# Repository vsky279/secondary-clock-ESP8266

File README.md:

# Driving secondary clock by ESP8266

Check out this Youtube [video](http://www.youtube.com/watch?v=zKabXwngn9Y) to see the clock in work.

## Intro

I have received this beautiful secondary clock [IPJ0612](https://www.pragotron.sk/?ukaz=content/ipj0612) produced by Czech company Pragotron in 80's. Secondary here means that the clock is only a "display" and has to receive signals from a central clock to move by one minute.

The clock is driven by kind of a stepper motor, powered by 24V. It has two wires as input directly connected to the coil. For one half turn an impulse of 24V is required for the remaining half turn -24V are applied.

## Electronics

We needed to use a circuit that can revert the voltage on its output. Two inputs are connected to ESP8266 GPIOs (GPIO0 and GPIO2). GPIO0 set to high makes 24V on output. Setting GPIO2 high causes -24V on output. A pull-up resistors are connected to GPIOs so that ESP8266 boots in desired 'normal operation' mode. A protection transistor (QX on the scheme) for accidental highs on both inputs has been added. The ESP8266 ESP-01 version is used.

We have used Eagle to draw the [scheme](./hw/driver.sch) and design the [board](./hw/board.sch).

To get the 3.3 voltage to power the ESP8266 a LM1085IT-3.3 TO220 regulator is used.
In my implementation, I'm using step-down module as I had one spare at home (the component with annoying blue LED on the pictures below). It's sold on eBay and can be found as [3A 9V/12V/19V To 3.3V DC-DC USB Step Down Buck Power Supply Module For Car](https://www.ebay.com/sch/i.html?_odkw=2pcs+3A+9V%2F12V%2F19V+To+3.3V+DC-DC+USB+Step+Down+Buck+Power+Supply+Module+For+Car&_osacat=0&_from=R40&_trksid=p2045573.m570.l1313.TR0.TRC0.H0.X3A+9V%2F12V%2F19V+To+3.3V+DC-DC+USB+Step+Down+Buck+Power+Supply+Module+For+Car.TRS0&_nkw=3A+9V%2F12V%2F19V+To+3.3V+DC-DC+USB+Step+Down+Buck+Power+Supply+Module+For+Car&_sacat=0). 

## Programming

I am using NodeMCU Lua ([https://github.com/nodemcu/nodemcu-firmware](https://github.com/nodemcu/nodemcu-firmware)) to program the ESP8266. The programming in Lua is very easy so the core program can have less than 140 lines including the web server used to adjust the clock.

A [NodeMCU custom builds](https://nodemcu-build.com/) tool can be used to compile the binary for ESP8266. Beside standard modules the following modules are used: `cron, enduser_setup, rtctime, sntp`. I have used the integer version of the firmware is used. Though float version should be fine too.

I am using [ESP8266 Flasher](https://github.com/nodemcu/nodemcu-flasher) to flash the binary.

To upload Lua files and files used by the web server the [ESPlorer](https://esp8266.ru/esplorer/) GUI can be used.

The program connects to the WIFI, regularly synchronizes time via NTP and sends 300ms to GPIO0 and GPIO1 alternately. To show correct time ESP needs to know what time the clock is showing at startup so it can set it to actual time. This can be adjusted in web browser as the ESP8266 is running a web server. Otherwise the clock assumes correct time is displayed and sends signals as time goes on.

It exposes also a telnet server so an OTA-like update of Lua codes can be performed.

In my implementation am using only 18V to run the clock (a power adapter from an old printer). With 24V the signal could probably be shorter than 300ms so clock adjustment would be faster.

The source code is in the folder [lua_code](https://github.com/vsky279/secondary-clock-ESP8266/tree/master/lua_code).

## Assembly

A 3d printed [holder](./holder/holder.skp) (designed in SketchUp) and double face duck tape has been used to mount the board inside the clock. An [STL file](./holder/holder.stl) is usually used in the slicer software.

I have also designed a cap to cover the hole of the original connector ([SketchUp file](./hw/holder/cap.skp) and [STL file](./holder/cap.stl)) - not shown on any of photos.

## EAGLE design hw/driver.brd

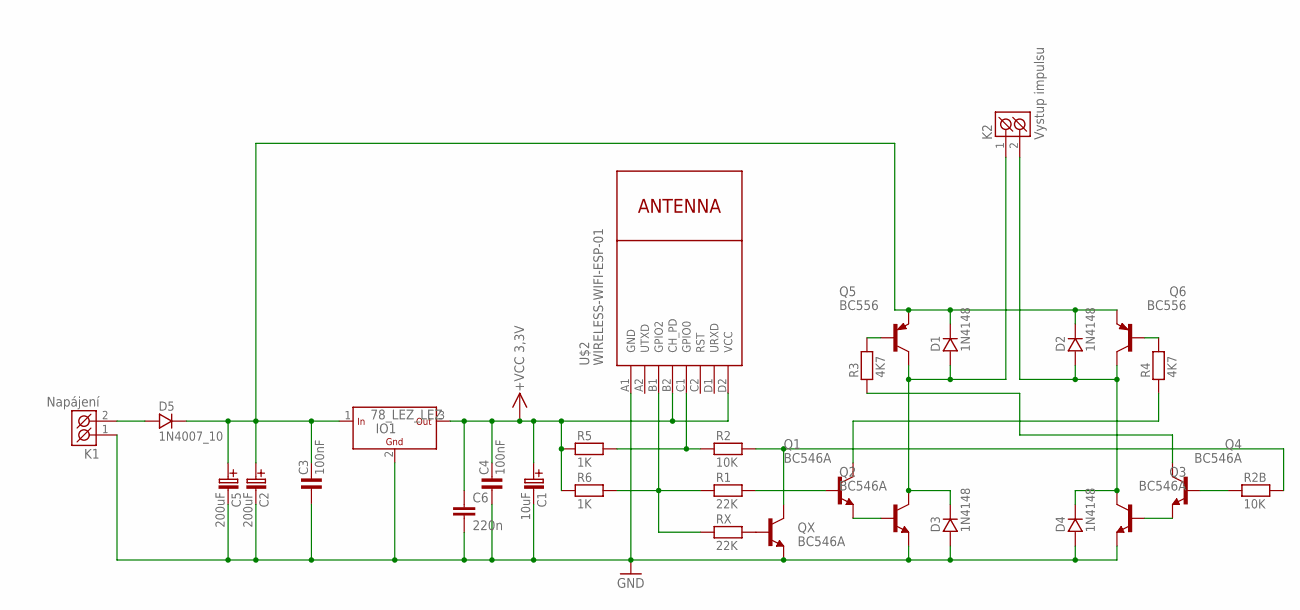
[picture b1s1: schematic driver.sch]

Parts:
C1: 10uF; C-EL_2,5
C2, C5: 200uF; C-EL_5
C3, C4: 100nF; C-5
C6: 220n; C1206
D1, D2, D3, D4: 1N4148; DO35
D5: 1N4007_10; DO41
IO1: 78_LEZ_LEZ; TO-220
K1: Napájení; CZM_5/2
K2: Vystup impulsu; CZM_5/2
Q1, Q2, Q3, Q4: BC546A; TO92-EBC
Q5, Q6: BC556; TO92-EBC
QX: BC546A; TO92-EBC
R1: 22K; R-10
R2, R2B: 10K; R-10
R3, R4: 4K7; R-10
R5, R6: 1K; R-10
RX: 22K; R-10
U$2: WIRELESS-WIFI-ESP-01

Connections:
GND: C1.C- (C_EL-), C2.C- (C_EL-), C3.1, C4.1, C5.C- (C_EL-), C6.2, D3.A, D4.A, IO1.2 (GND), K1.1 (K1), Q2.E, Q3.E, QX.E, U$2.A1 (GND)
unnamed: D2.A, D4.K, K2.2 (K2), Q3.C, Q6.C
unnamed: D1.A, D3.K, K2.1 (K1), Q2.C, Q5.C
unnamed: C2.C+ (C_EL+), C3.2, C5.C+ (C_EL+), D1.K, D2.K, D5.K, IO1.1 (IN), Q5.E, Q6.E
unnamed: Q5.B, R3.2
unnamed: Q6.B, R4.2
unnamed: Q4.C, R3.1
unnamed: Q1.C, R4.1
unnamed: Q4.B, R2B.1
unnamed: Q3.B, Q4.E
unnamed: Q1.E, Q2.B
unnamed: D5.A, K1.2 (K2)
unnamed: Q1.B, R1.2
unnamed: R1.1, R6.2, RX.1, U$2.B1 (GPIO2)
unnamed: QX.C, R2.2, R2B.2
unnamed: R2.1, R5.2, U$2.C1 (GPIO0)
unnamed: QX.B, RX.2
VCC: C1.C+ (C_EL+), C4.2, C6.1, IO1.3 (OUT), R5.1, R6.1, U$2.B2 (CH_PD), U$2.D2 (VCC)

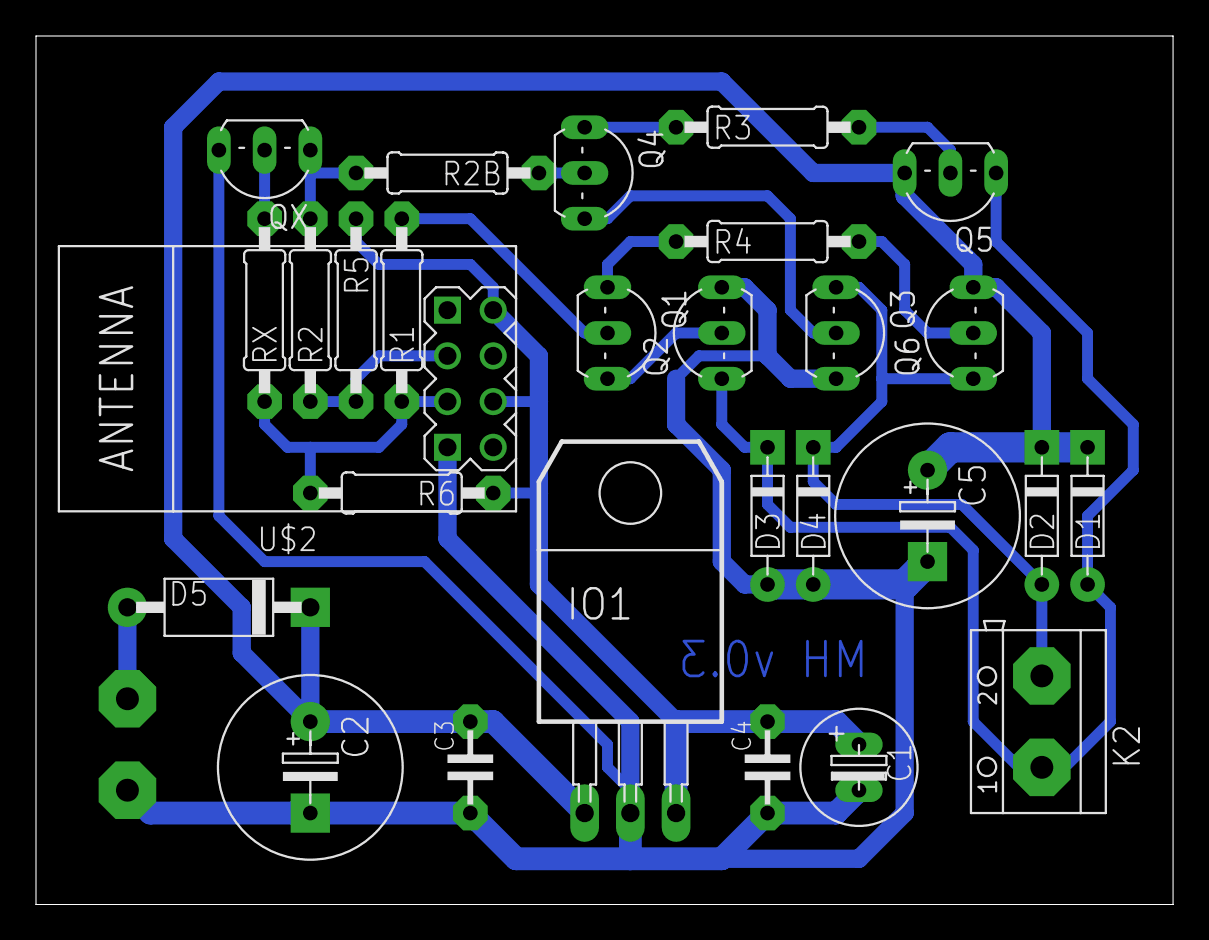
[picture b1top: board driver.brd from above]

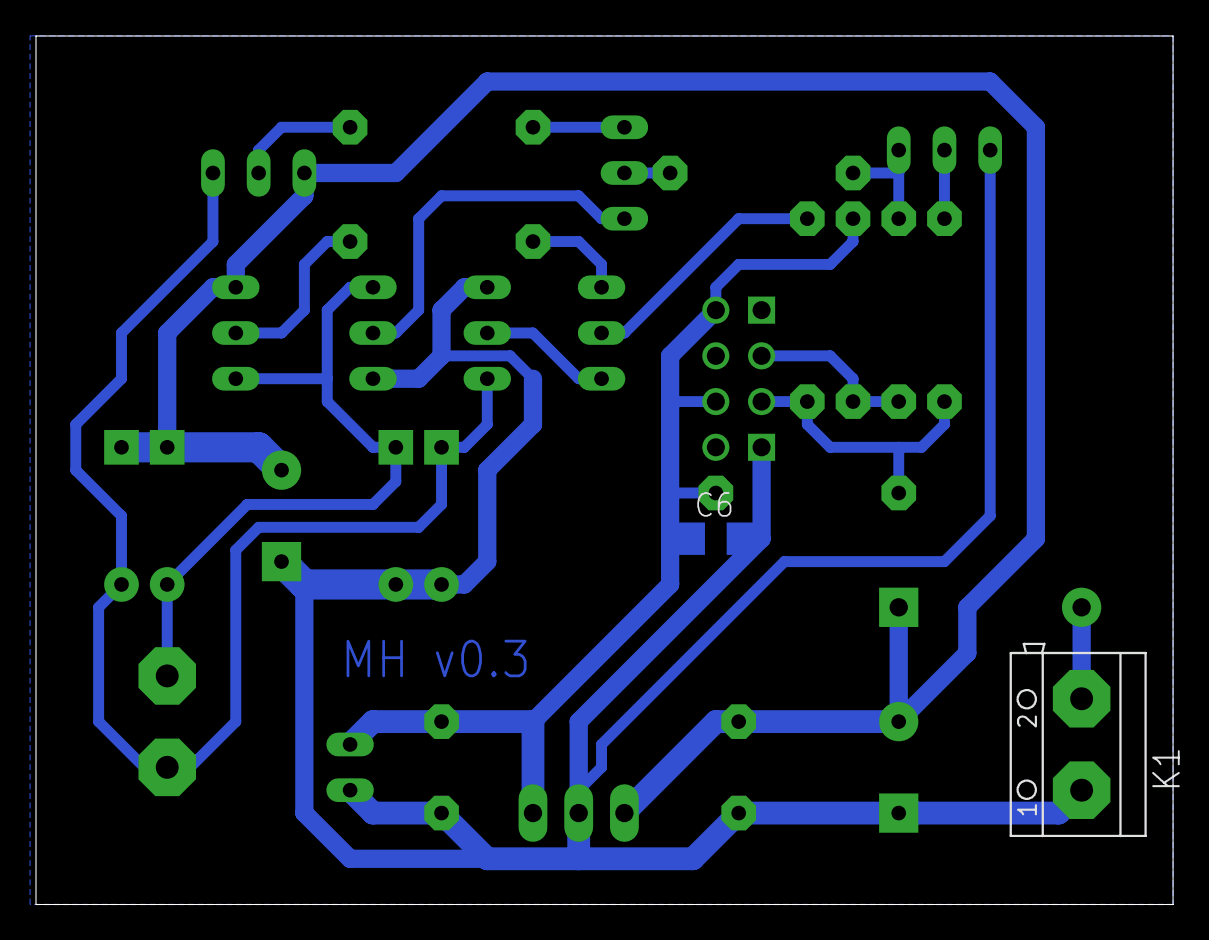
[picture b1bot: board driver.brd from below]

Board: 2 copper layers, 63.2 x 48.2 mm, 30 parts (2 on the bottom side), 18 nets.

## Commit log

2017-10-15 :lollipop: Added .gitattributes
2018-11-04 Daylight saving time perfection (before dst is canceled?)

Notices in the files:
parts and their libraries:
Copyright (C) PaJa 2001-2010
diy-modules: Released under the Creative Commons Attribution 4.0 International License: http://creativecommons.org/licenses/by/4.0
